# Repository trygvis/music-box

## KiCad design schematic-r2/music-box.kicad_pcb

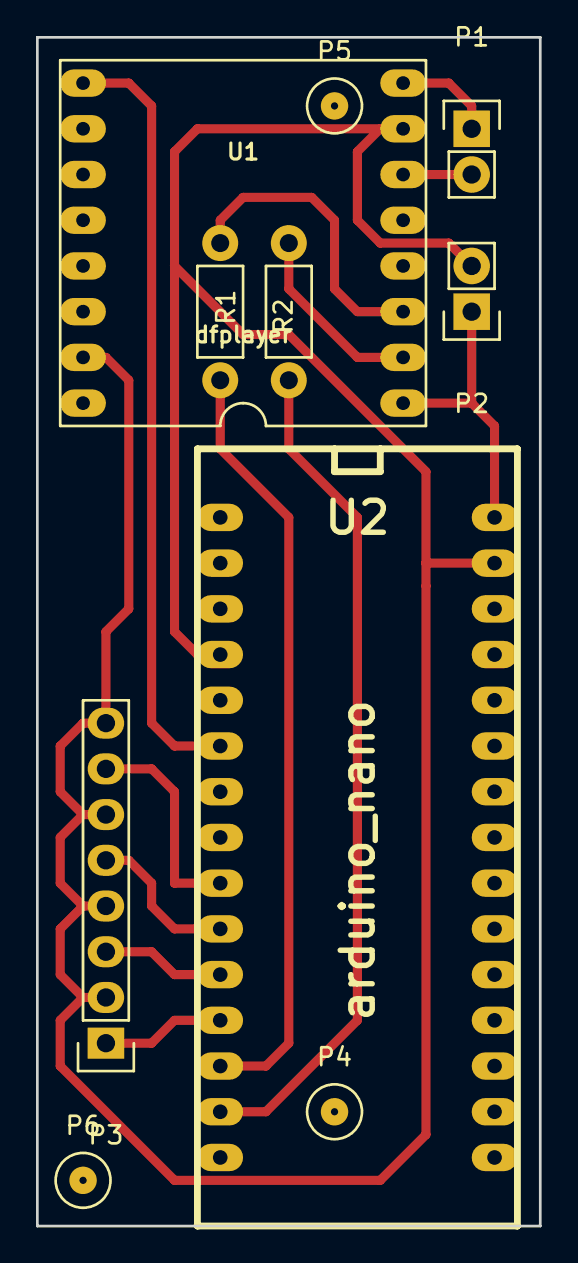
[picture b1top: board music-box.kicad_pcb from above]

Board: 2 copper layers, 27.9 x 66.0 mm, 10 parts (0 on the bottom side), 13 nets.

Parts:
P1: Speaker; Pin_Header_Straight_1x02
P2: Power; Pin_Header_Straight_1x02
P3: Buttons; Pin_Header_Straight_1x08
P4: Alignment 1; alignment
P5: Alignment 2; alignment
P6: Alignment 3; alignment
R1, R2: 1k; Resistor_Horizontal_RM7mm
U1: dfplayer; DFPlayer
U2: arduino_nano

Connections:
+5V: P2.1, U1.1, U2.30
/BUSY: U1.16, U2.6
/BUTTON_A: P3.7, U2.9
/BUTTON_B: P3.5, U2.10
/BUTTON_C: P3.3, U2.11
/BUTTON_D: P3.1, U2.12
/MCU_RX: R2.2, U2.13
/MCU_TX: R1.1, U2.14
/MP3_RX: R1.2, U1.2
/MP3_TX: R2.1, U1.3
/SPEAKER_1: P1.2, U1.6
/SPEAKER_2: P1.1, U1.8
GND: P2.2, P3.2, P3.4, P3.6, P3.8, U1.7, U1.10, U2.4, U2.29

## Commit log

2016-07-07 o Initial import of schematic and FreeCAD model.
2016-07-07 o Missing files.
2016-07-07 Add arduino code
2016-07-10 o Production plots and code for the first board.
2016-07-10 o Revision 2. Fixing too wide DF player footprint, single-side only.
